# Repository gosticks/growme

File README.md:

# GrowMe

GrowMe is a state-of-the-art progress tracking app that makes your accomplishments come alive. With the help of a cybertronically enhanced plant, it tracks your real-time progress and milestones, showcasing them as a visual representation of your achievements and setbacks.

## Team

As part of the Unternehmer TUM Think.Make.Start program, this innovative project was developed in just two weeks, and I was proud to be part of the software development team. Our team worked hand-in-hand with the hardware team to bring this unique idea to life. While they focused on the plant mechanics, I was responsible for the ESP32 microcontroller that controls the plant and the connected mobile app.

## Technology

The cybertronically enhanced plant is powered by the ESP32 microcontroller, which operates its six motors to produce stunning animations. The app, developed in Flutter, connects to the ESP32 through Bluetooth Low Energy and provides users with full control over the plant and its animations. Whether you are a seasoned gardener or a novice, GrowMe will take your life goal journey to the next level.

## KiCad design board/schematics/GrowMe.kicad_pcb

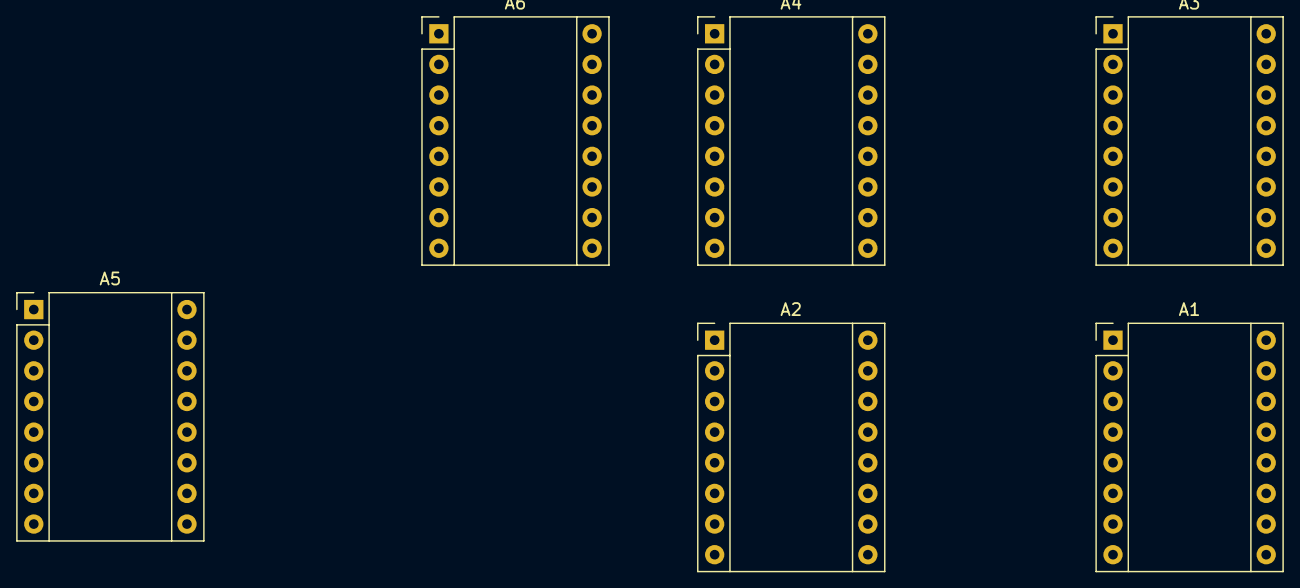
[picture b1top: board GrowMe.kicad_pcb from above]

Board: 2 copper layers, 6 parts (0 on the bottom side), 5 nets, no tracks yet.

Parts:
A1, A2, A3, A4, A5, A6: M1_A4988; Pololu_Breakout-16_15.2x20.3mm

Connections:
+3V3: A1.2 (VDD), A2.2 (VDD), A3.2 (VDD), A4.2 (VDD), A5.2 (VDD), A6.2 (VDD)
+5V: A1.8 (VMOT), A2.8 (VMOT), A3.8 (VMOT), A4.8 (VMOT), A5.8 (VMOT), A6.8 (VMOT)
GND: A1.1 (GND), A1.7 (GND), A2.1 (GND), A2.7 (GND), A3.1 (GND), A3.7 (GND), A4.1 (GND), A4.7 (GND), A5.1 (GND), A5.7 (GND), A6.1 (GND), A6.7 (GND)
M_EN: A1.9 (~ENABLE), A2.9 (~ENABLE), A3.9 (~ENABLE), A4.9 (~ENABLE), A5.9 (~ENABLE), A6.9 (~ENABLE)
M_SLP_RST: A1.13 (~RESET), A1.14 (~SLEEP), A2.13 (~RESET), A2.14 (~SLEEP), A3.13 (~RESET), A3.14 (~SLEEP), A4.13 (~RESET), A4.14 (~SLEEP), A5.13 (~RESET), A5.14 (~SLEEP), A6.13 (~RESET), A6.14 (~SLEEP)

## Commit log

2022-09-24 WIP: initial project setup
2022-09-25 wip: initial motor test
2022-09-25 wip: initial PCB layout
2022-09-25 feat: add initial schematic
2022-09-25 fix: respect schematic motor assignments
2022-09-25 feat: update sheet layout
2022-09-26 feat: add control for all 6 motors
2022-09-26 feat: update power management
2022-09-26 feat: add formatter
2022-09-26 chore: run formatter
2022-09-26 feat: add protobuf setup
2022-09-26 feat: add PD power sheets
2022-09-26 chore: add assets
2022-09-26 feat: initial app setup
2022-09-26 feat: initial BT classic setup
2022-09-27 feat: add initial card app layout
2022-09-28 feat: enable full app motor controlls
2022-09-29 feat: enable device reconnection
2022-09-29 feat: update layout
2022-09-29 feat: add slower motor movement speed
2022-09-30 feat: add final project code
2022-09-30 feat: add semaphore
2022-09-30 fix: remove semas
2022-09-30 fix: revert motor step to normal
2022-09-30 fix: remove sema for bt operation
2022-09-30 feat: update debug view
2022-09-30 feat: improve layout on smaller phones
2022-09-30 feat: improve mobile layout
2022-09-30 feat: improve layout
